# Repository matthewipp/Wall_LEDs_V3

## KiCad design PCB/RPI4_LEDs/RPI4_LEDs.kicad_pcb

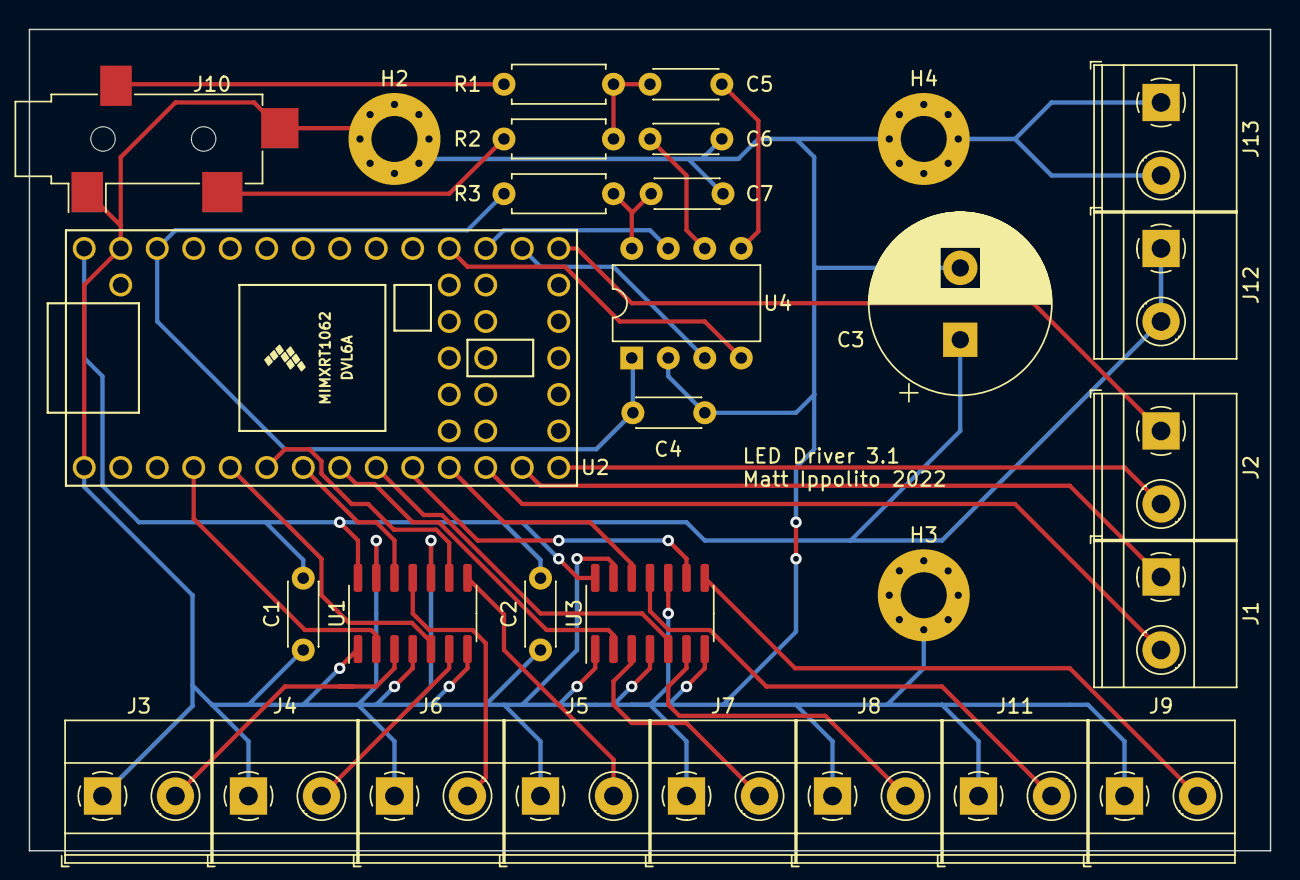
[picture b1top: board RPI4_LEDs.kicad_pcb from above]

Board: 2 copper layers, 86.4 x 57.2 mm, 30 parts (0 on the bottom side), 32 nets.

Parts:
C1, C2, C4, C5, C6: 0.1u; C_Disc_D4.3mm_W1.9mm_P5.00mm
C3: 1000u; CP_Radial_D12.5mm_P5.00mm
C7: 30p; C_Disc_D4.3mm_W1.9mm_P5.00mm
H2, H3, H4: MountingHole; MountingHole_3.2mm_M3_Pad_Via
J1, J2, J3, J4, J5, J6, J7, J8, J9, J11, J12, J13: Screw_Terminal_01x02; TerminalBlock_Phoenix_MKDS-1,5-2-5.08_1x02_P5.08mm_Horizont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
J10: AudioJack4; Jack_3.5mm_CUI_SJ-3524-SMT_Horizontal
R1, R2: 22k; R_Axial_DIN0207_L6.3mm_D2.5mm_P7.62mm_Horizontal
R3: 220k; R_Axial_DIN0207_L6.3mm_D2.5mm_P7.62mm_Horizontal
U1, U3: SN74HCT125; SOIC-14_3.9x8.7mm_P1.27mm
U2: Teensy4.0; Teensy40
U4: MSGEQ7; DIP-8_W7.62mm

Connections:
+3V3: C4.2, R3.2, U2.31, U4.1
+5V: C1.2, C2.2, C3.1, J12.1, J12.2, U1.14, U2.33, U3.14
/CS: J1.2, U2.12
/Equalizer_Out: U2.21, U4.3
/LED_0: J3.2, U1.3
/LED_0_3V3: U1.2, U2.4
/LED_1: J4.2, U1.6
/LED_1_3V3: U1.5, U2.5
/LED_2: J5.2, U1.8
/LED_2_3V3: U1.9, U2.6
/LED_3: J6.2, U1.11
/LED_3_3V3: U1.12, U2.7
/LED_4: J7.2, U3.3
/LED_4_3V3: U2.8, U3.2
/LED_5: J8.2, U3.6
/LED_5_3V3: U2.9, U3.5
/LED_6: J9.2, U3.8
/LED_6_3V3: U2.10, U3.9
/LED_7: J11.2, U3.11
/LED_7_3V3: U2.11, U3.12
/Left: J10.R1, R1.2
/MISO: J2.2, U2.14
/MOSI: J1.1, U2.13
/Reset_Equalizer: U2.22, U4.7
/Right: J10.T, R2.2
/SCK: J2.1, U2.20
/Strobe: U2.23, U4.4
GNDREF: C1.1, C2.1, C3.2, C4.1, C6.2, C7.1, H2.1, H3.1, H4.1, J3.1, J4.1, J5.1, J6.1, J7.1, J8.1, J9.1, J10.R2, J10.S, J11.1, J13.1, J13.2, U1.1, U1.4, U1.7, U1.10, U1.13, U2.1, U2.32, U3.1, U3.4, U3.7, U3.10, U3.13, U4.2
unnamed: C5.1, R1.1, R2.1
unnamed: C5.2, U4.5
unnamed: C6.1, U4.6
unnamed: C7.2, R3.1, U4.8

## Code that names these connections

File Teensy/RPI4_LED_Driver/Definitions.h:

/*
 * author: Matt Ippolito
 * date-created: 7/20/2022
 * last-modified: 7/20/2022
 * 
 * Definitions.h
 * Definitions for RPi4 LEDs
 */

#ifndef DEFINITIONS_H
#define DEFINITIONS_H

// LED Settings
#define LED_COLOR_ORDER WS2811_GRB
#define LED_SPEED WS2811_800kHz
#define LED_LENGTH 300
#define NUM_LED_STRIPS 8
#define NUM_LEDS 2400
#define BYTES_PER_LED 3
#define BYTES_PER_INT 4
// Pin Definitions
#define LED_0_PIN 2
#define LED_1_PIN 3
#define LED_2_PIN 5
#define LED_3_PIN 4
#define LED_4_PIN 6
#define LED_5_PIN 7
#define LED_6_PIN 9
#define LED_7_PIN 8
#define RPI_CS 10
#define RPI_COPI 11
#define RPI_CIPO 12
#define RPI_SCK 13
#define EQUALIZER_OUT A0
#define EQUALIZER_RESET A1
#define EQUALIZER_STROBE A2
#define FREQ_BUFFER_LEN 5
//#define DEBUG

#endif
 

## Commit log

2022-08-07 Added all files
2022-08-08 Fixed compatibility issues for linux GUI
2022-08-08 Fixed gitignore
2022-08-15 SolidColor ready for SPI testing
2022-08-15 Added GPIO code
2022-08-16 Started Changing SPI to Serial
2022-08-16 Added serial stuff to teensy
2022-08-16 Fixed SPIManager
2022-08-21 Working and on wall.
2022-08-21 Added spotify API
